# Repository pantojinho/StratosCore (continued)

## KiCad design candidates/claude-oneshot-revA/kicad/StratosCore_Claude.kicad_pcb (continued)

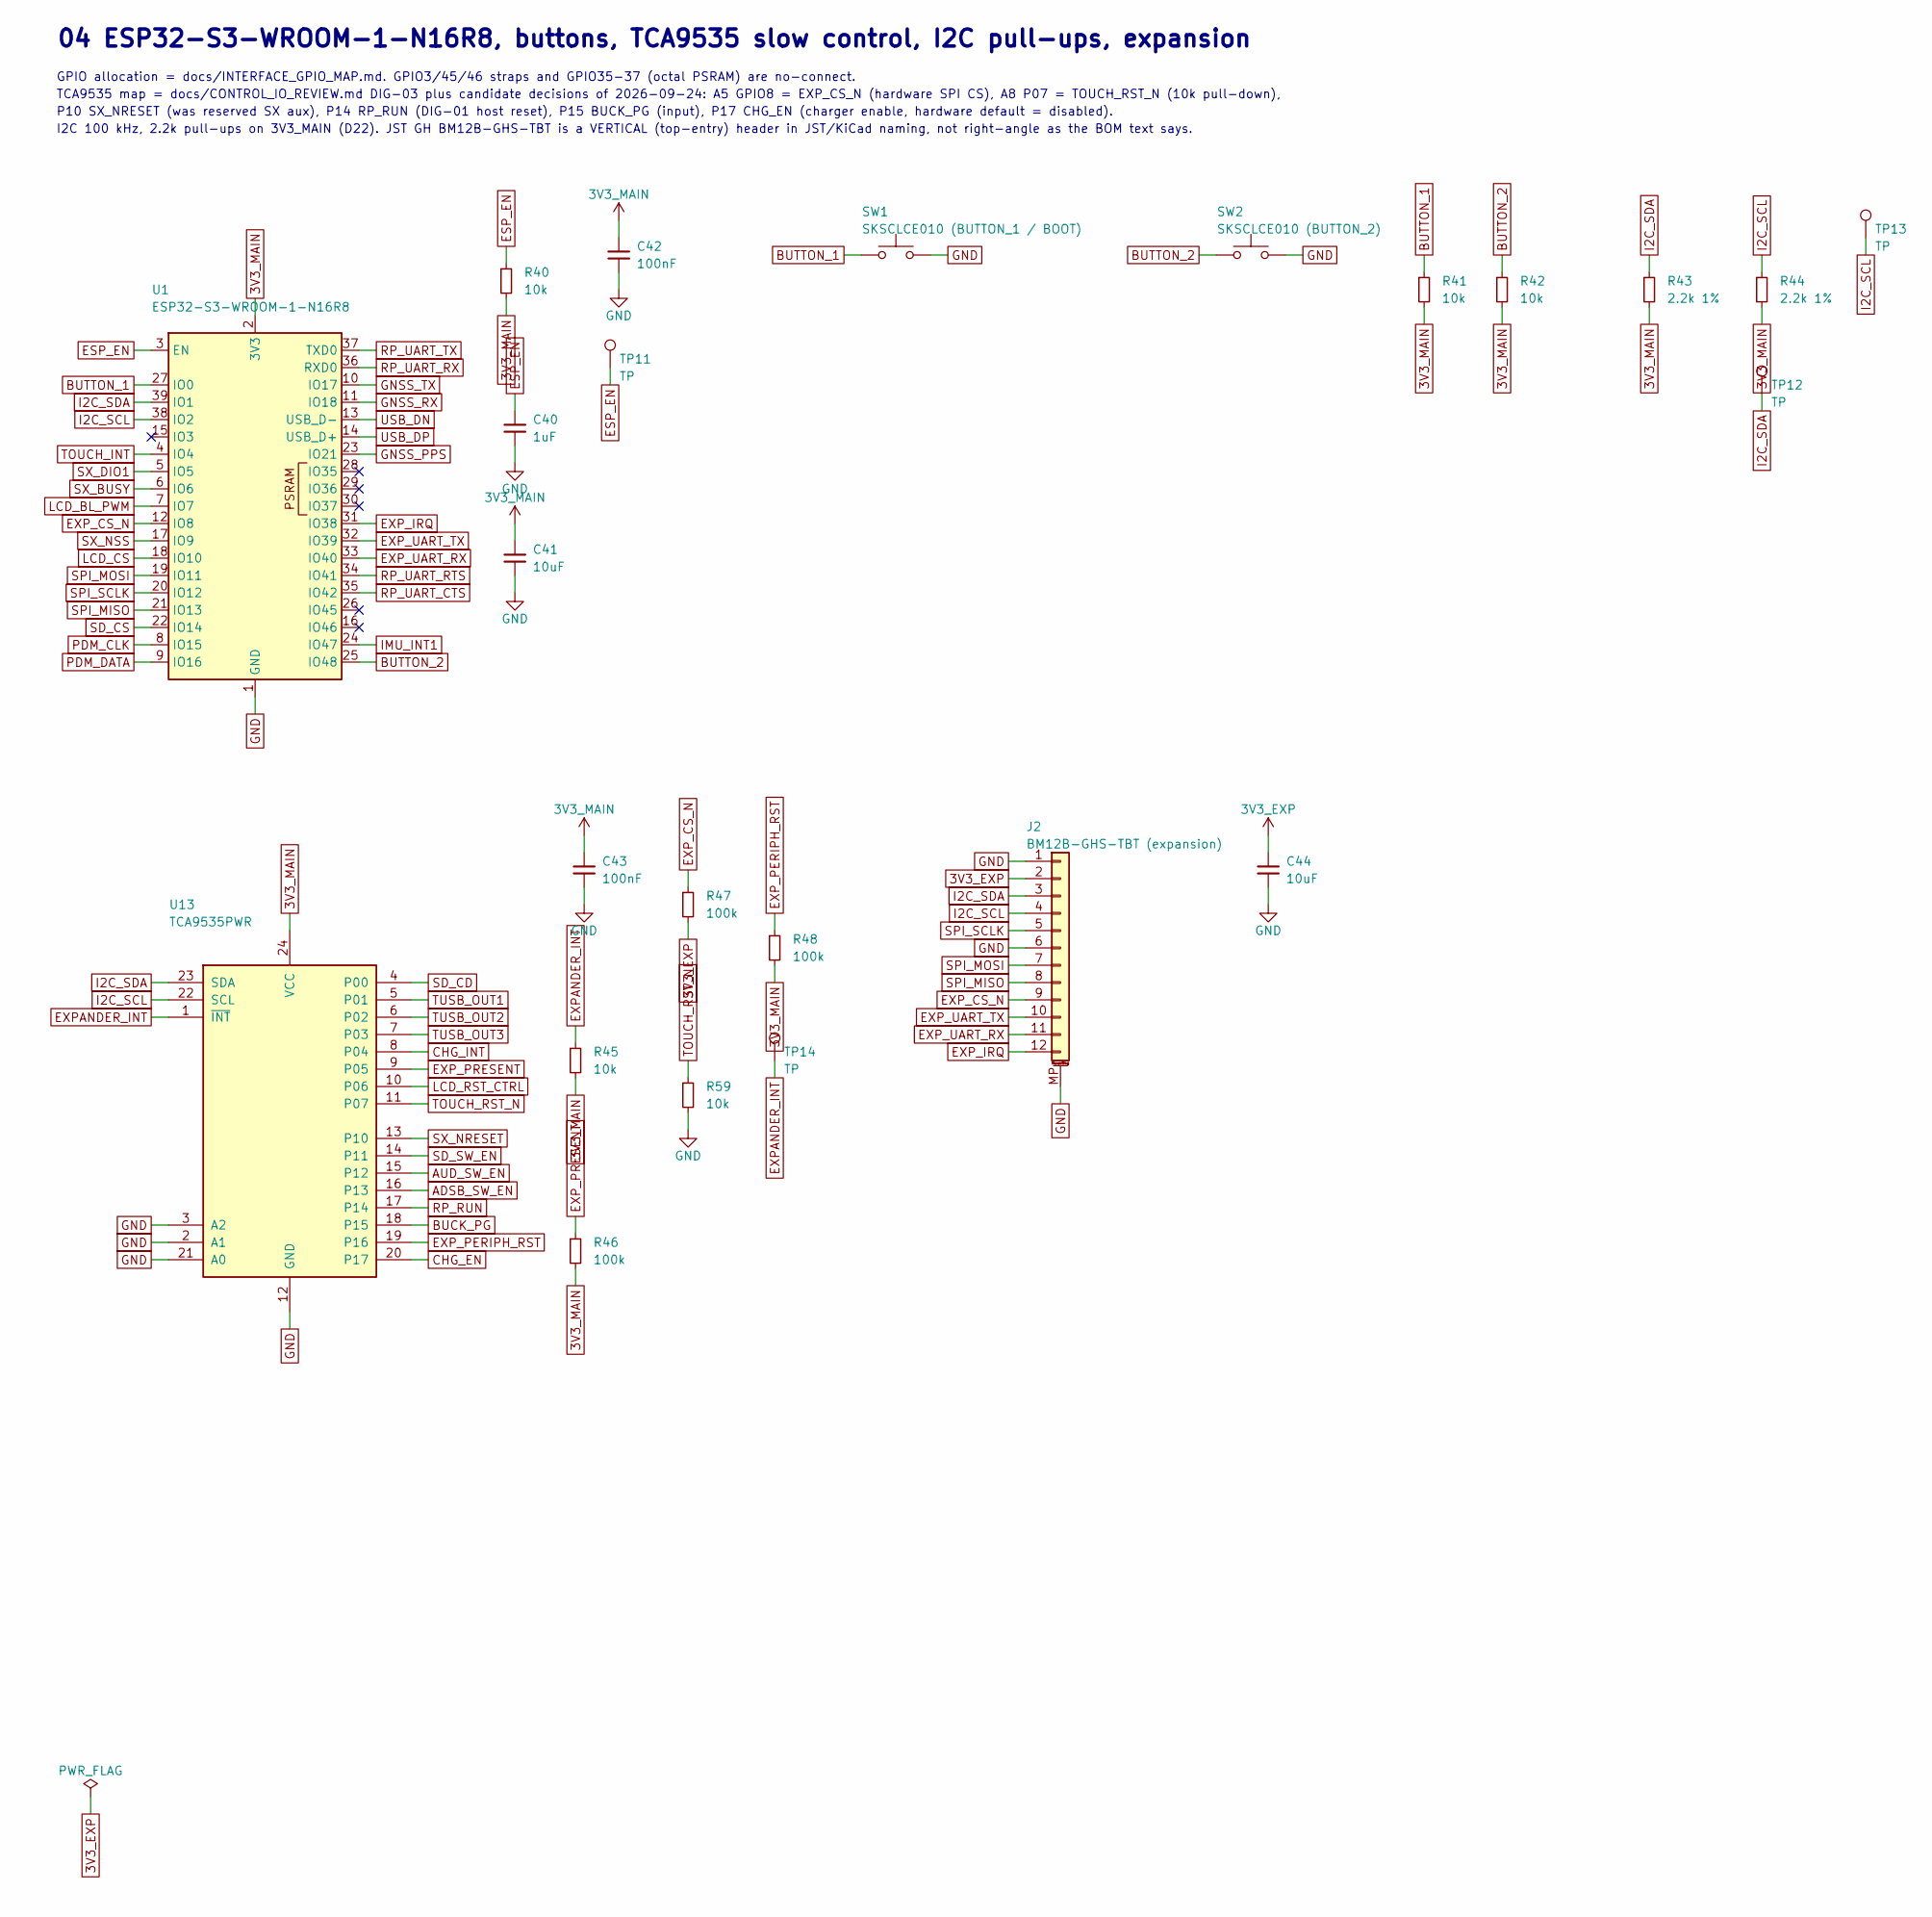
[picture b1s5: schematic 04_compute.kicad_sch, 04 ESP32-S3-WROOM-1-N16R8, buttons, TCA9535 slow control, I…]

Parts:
C40: 1uF; C_0402_1005Metric
C41, C44: 10uF; C_0603_1608Metric
C42, C43: 100nF; C_0402_1005Metric
J2: BM12B-GHS-TBT (expansion); JST_GH_BM12B-GHS-TBT_1x12-1MP_P1.25mm_Vertical; MPN BM12B-GHS-TBT
R40, R41, R42, R45, R59: 10k; R_0402_1005Metric
R43, R44: 2.2k 1%; R_0402_1005Metric
R46, R47, R48: 100k; R_0402_1005Metric
SW1: SKSCLCE010 (BUTTON_1 / BOOT); SW_Alps_SKSCLCE010_SidePush; MPN SKSCLCE010
SW2: SKSCLCE010 (BUTTON_2); SW_Alps_SKSCLCE010_SidePush; MPN SKSCLCE010
TP11, TP12, TP13, TP14: TP; TestPoint_Pad_D1.0mm
U1: ESP32-S3-WROOM-1-N16R8; ESP32-S3-WROOM-1; MPN ESP32-S3-WROOM-1-N16R8
U13: TCA9535PWR; TI_PW0024A_TSSOP-24_4.4x7.8mm_TCA9535; MPN TCA9535PWR

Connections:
3V3_EXP: C44.1, J2.2, R47.2; also elsewhere on the board
3V3_MAIN: C41.1, C42.1, C43.1, R40.2, R41.2, R42.2, R43.2, R44.2, R45.2, R46.2, R48.2, U1.2 (3V3), U13.24 (VCC); also elsewhere on the board
ADSB_SW_EN: U13.16 (P13); also elsewhere on the board
AUD_SW_EN: U13.15 (P12); also elsewhere on the board
BUCK_PG: U13.18 (P15); also elsewhere on the board
BUTTON_1: R41.1, SW1.1, U1.27 (IO0)
BUTTON_2: R42.1, SW2.1, U1.25 (IO48)
CHG_EN: U13.20 (P17); also elsewhere on the board
CHG_INT: U13.8 (P04); also elsewhere on the board
ESP_EN: C40.1, R40.1, TP11.1, U1.3 (EN)
EXPANDER_INT: R45.1, TP14.1, U13.1 (~INT)
EXP_CS_N: J2.9, R47.1, U1.12 (IO8)
EXP_IRQ: J2.12, U1.31 (IO38)
EXP_PERIPH_RST: R48.1, U13.19 (P16)
EXP_PRESENT: R46.1, U13.9 (P05)
EXP_UART_RX: J2.11, U1.33 (IO40)
EXP_UART_TX: J2.10, U1.32 (IO39)
GND: C40.2, C41.2, C42.2, C43.2, C44.2, J2.1, J2.6, J2.MP (MountPin), R59.2, SW1.2, SW2.2, U1.1 (GND), U1.40 (GND), U1.41 (GND), U13.2 (A1), U13.3 (A2), U13.12 (GND), U13.21 (A0); also elsewhere on the board
GNSS_PPS: U1.23 (IO21); also elsewhere on the board
GNSS_RX: U1.11 (IO18); also elsewhere on the board
GNSS_TX: U1.10 (IO17); also elsewhere on the board
I2C_SCL: J2.4, R44.1, TP13.1, U1.38 (IO2), U13.22 (SCL); also elsewhere on the board
I2C_SDA: J2.3, R43.1, TP12.1, U1.39 (IO1), U13.23 (SDA); also elsewhere on the board
IMU_INT1: U1.24 (IO47); also elsewhere on the board
LCD_BL_PWM: U1.7 (IO7); also elsewhere on the board
LCD_CS: U1.18 (IO10); also elsewhere on the board
LCD_RST_CTRL: U13.10 (P06); also elsewhere on the board
PDM_CLK: U1.8 (IO15); also elsewhere on the board
PDM_DATA: U1.9 (IO16); also elsewhere on the board
RP_RUN: U13.17 (P14); also elsewhere on the board
RP_UART_CTS: U1.35 (IO42); also elsewhere on the board
RP_UART_RTS: U1.34 (IO41); also elsewhere on the board
RP_UART_RX: U1.36 (RXD0); also elsewhere on the board
RP_UART_TX: U1.37 (TXD0); also elsewhere on the board
SD_CD: U13.4 (P00); also elsewhere on the board
SD_CS: U1.22 (IO14); also elsewhere on the board
SD_SW_EN: U13.14 (P11); also elsewhere on the board
SPI_MISO: J2.8, U1.21 (IO13); also elsewhere on the board
SPI_MOSI: J2.7, U1.19 (IO11); also elsewhere on the board
SPI_SCLK: J2.5, U1.20 (IO12); also elsewhere on the board
SX_BUSY: U1.6 (IO6); also elsewhere on the board
SX_DIO1: U1.5 (IO5); also elsewhere on the board
SX_NRESET: U13.13 (P10); also elsewhere on the board
SX_NSS: U1.17 (IO9); also elsewhere on the board
TOUCH_INT: U1.4 (IO4); also elsewhere on the board
TOUCH_RST_N: R59.1, U13.11 (P07); also elsewhere on the board
TUSB_OUT1: U13.5 (P01); also elsewhere on the board
TUSB_OUT2: U13.6 (P02); also elsewhere on the board
TUSB_OUT3: U13.7 (P03); also elsewhere on the board
USB_DN: U1.13 (USB_D-); also elsewhere on the board
USB_DP: U1.14 (USB_D+); also elsewhere on the board

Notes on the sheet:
04 ESP32-S3-WROOM-1-N16R8, buttons, TCA9535 slow control, I2C pull-ups, expansion
GPIO allocation = docs/INTERFACE_GPIO_MAP.md. GPIO3/45/46 straps and GPIO35-37 (octal PSRAM) are no-connect.
TCA9535 map = docs/CONTROL_IO_REVIEW.md DIG-03 plus candidate decisions of 2026-09-24: A5 GPIO8 = EXP_CS_N (hardware SPI CS), A8 P07 = TOUCH_RST_N (10k pull-down),
P10 SX_NRESET (was reserved SX aux), P14 RP_RUN (DIG-01 host reset), P15 BUCK_PG (input), P17 CHG_EN (charger enable, hardware default = disabled).
I2C 100 kHz, 2.2k pull-ups on 3V3_MAIN (D22). JST GH BM12B-GHS-TBT is a VERTICAL (top-entry) header in JST/KiCad naming, not right-angle as the BOM text says.

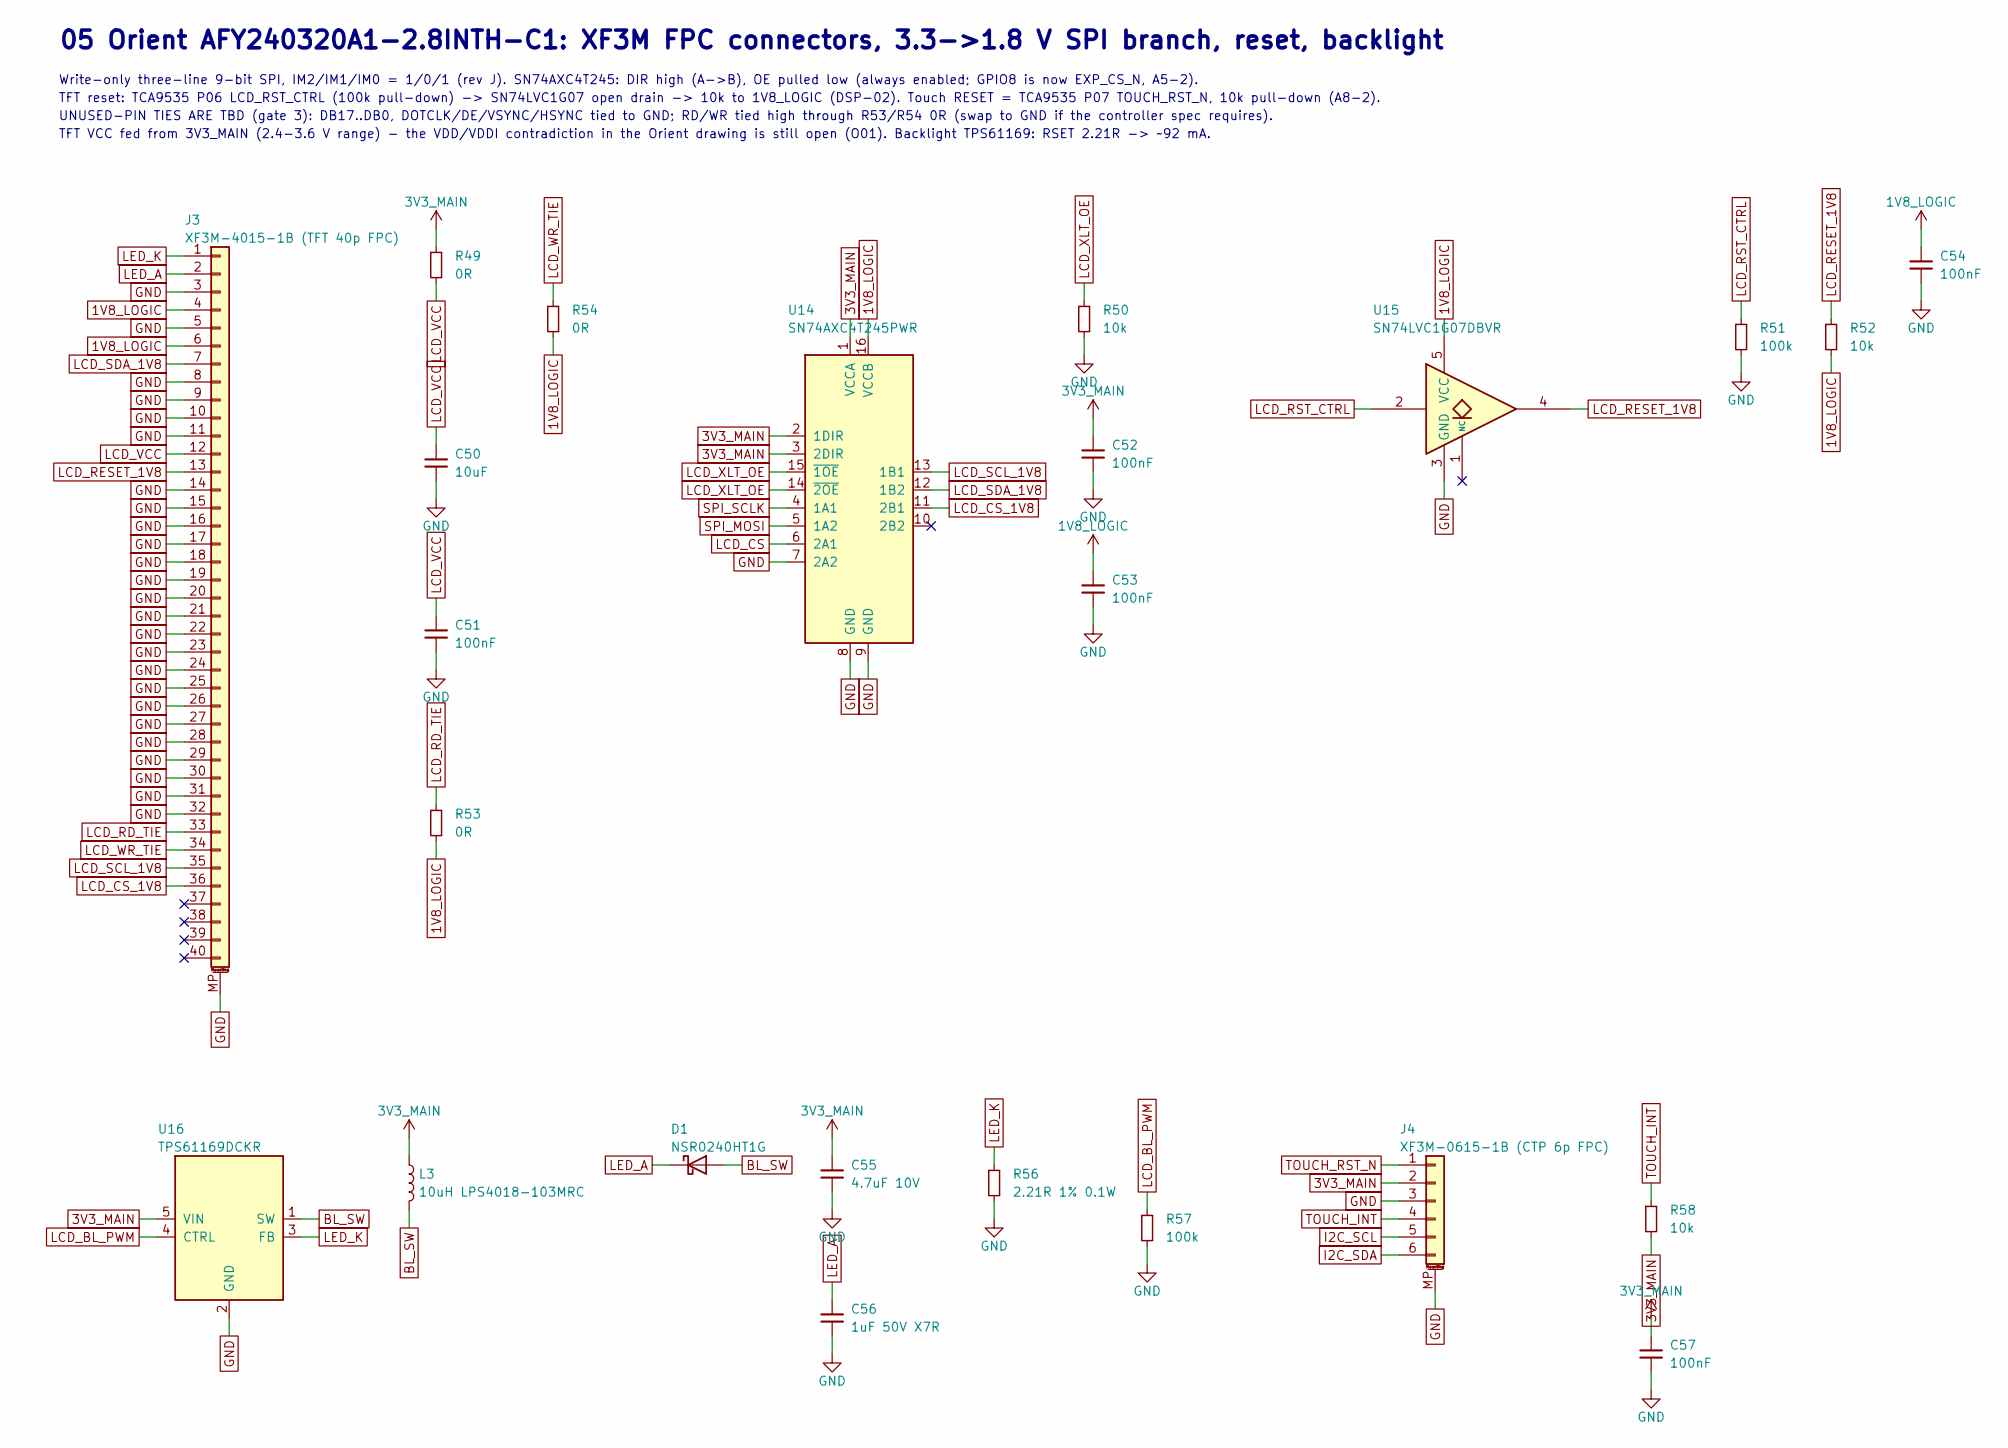
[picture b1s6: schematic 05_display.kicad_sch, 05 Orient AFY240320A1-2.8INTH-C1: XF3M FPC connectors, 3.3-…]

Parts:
C50: 10uF; C_0603_1608Metric
C51, C52, C53, C54, C57: 100nF; C_0402_1005Metric
C55: 4.7uF 10V; C_0603_1608Metric
C56: 1uF 50V X7R; C_0805_2012Metric
D1: NSR0240HT1G; D_SOD-323; MPN NSR0240HT1G
J3: XF3M-4015-1B (TFT 40p FPC); Omron_XF3M-4015-1B_1x40-1MP_P0.5mm_Horizontal; MPN XF3M-4015-1B
J4: XF3M-0615-1B (CTP 6p FPC); Omron_XF3M-0615-1B_1x06-1MP_P0.5mm_Horizontal; MPN XF3M-0615-1B
L3: 10uH LPS4018-103MRC; L_Coilcraft_LPS4018; MPN LPS4018-103MRC
R49: 0R; R_0603_1608Metric
R50, R52, R58: 10k; R_0402_1005Metric
R51, R57: 100k; R_0402_1005Metric
R53, R54: 0R; R_0402_1005Metric
R56: 2.21R 1% 0.1W; R_0603_1608Metric
U14: SN74AXC4T245PWR; TSSOP-16_4.4x5mm_P0.65mm; MPN SN74AXC4T245PWR
U15: SN74LVC1G07DBVR; SOT-23-5; MPN SN74LVC1G07DBVR
U16: TPS61169DCKR; TI_DCK0005A_SC-70-5_TPS61169; MPN TPS61169DCKR

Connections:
1V8_LOGIC: C53.1, C54.1, J3.4, J3.6, R52.2, R53.2, R54.2, U14.16 (VCCB), U15.5 (VCC); also elsewhere on the board
3V3_MAIN: C52.1, C55.1, C57.1, J4.2, L3.1, R49.1, R58.2, U14.1 (VCCA), U14.2 (1DIR), U14.3 (2DIR), U16.5 (VIN); also elsewhere on the board
BL_SW: D1.2 (A), L3.2, U16.1 (SW)
GND: C50.2, C51.2, C52.2, C53.2, C54.2, C55.2, C56.2, C57.2, J3.3, J3.5, J3.8, J3.9, J3.10, J3.11, J3.14, J3.15, J3.16, J3.17, J3.18, J3.19, J3.20, J3.21, J3.22, J3.23, J3.24, J3.25, J3.26, J3.27, J3.28, J3.29, J3.30, J3.31, J3.32, J3.MP (MountPin), J4.3, J4.MP (MountPin), R50.2, R51.2, R56.2, R57.2, U14.7 (2A2), U14.8 (GND), U14.9 (GND), U15.3 (GND), U16.2 (GND); also elsewhere on the board
I2C_SCL: J4.5; also elsewhere on the board
I2C_SDA: J4.6; also elsewhere on the board
LCD_BL_PWM: R57.1, U16.4 (CTRL); also elsewhere on the board
LCD_CS: U14.6 (2A1); also elsewhere on the board
LCD_CS_1V8: J3.36, U14.11 (2B1)
LCD_RD_TIE: J3.33, R53.1
LCD_RESET_1V8: J3.13, R52.1, U15.4
LCD_RST_CTRL: R51.1, U15.2; also elsewhere on the board
LCD_SCL_1V8: J3.35, U14.13 (1B1)
LCD_SDA_1V8: J3.7, U14.12 (1B2)
LCD_VCC: C50.1, C51.1, J3.12, R49.2
LCD_WR_TIE: J3.34, R54.1
LCD_XLT_OE: R50.1, U14.14 (~2OE), U14.15 (~1OE)
LED_A: C56.1, D1.1 (K), J3.2
LED_K: J3.1, R56.1, U16.3 (FB)
SPI_MOSI: U14.5 (1A2); also elsewhere on the board
SPI_SCLK: U14.4 (1A1); also elsewhere on the board
TOUCH_INT: J4.4, R58.1; also elsewhere on the board
TOUCH_RST_N: J4.1; also elsewhere on the board

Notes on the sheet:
05 Orient AFY240320A1-2.8INTH-C1: XF3M FPC connectors, 3.3->1.8 V SPI branch, reset, backlight
Write-only three-line 9-bit SPI, IM2/IM1/IM0 = 1/0/1 (rev J). SN74AXC4T245: DIR high (A->B), OE pulled low (always enabled; GPIO8 is now EXP_CS_N, A5-2).
TFT reset: TCA9535 P06 LCD_RST_CTRL (100k pull-down) -> SN74LVC1G07 open drain -> 10k to 1V8_LOGIC (DSP-02). Touch RESET = TCA9535 P07 TOUCH_RST_N, 10k pull-down (A8-2).
UNUSED-PIN TIES ARE TBD (gate 3): DB17..DB0, DOTCLK/DE/VSYNC/HSYNC tied to GND; RD/WR tied high through R53/R54 0R (swap to GND if the controller spec requires).
TFT VCC fed from 3V3_MAIN (2.4-3.6 V range) - the VDD/VDDI contradiction in the Orient drawing is still open (O01). Backlight TPS61169: RSET 2.21R -> ~92 mA.

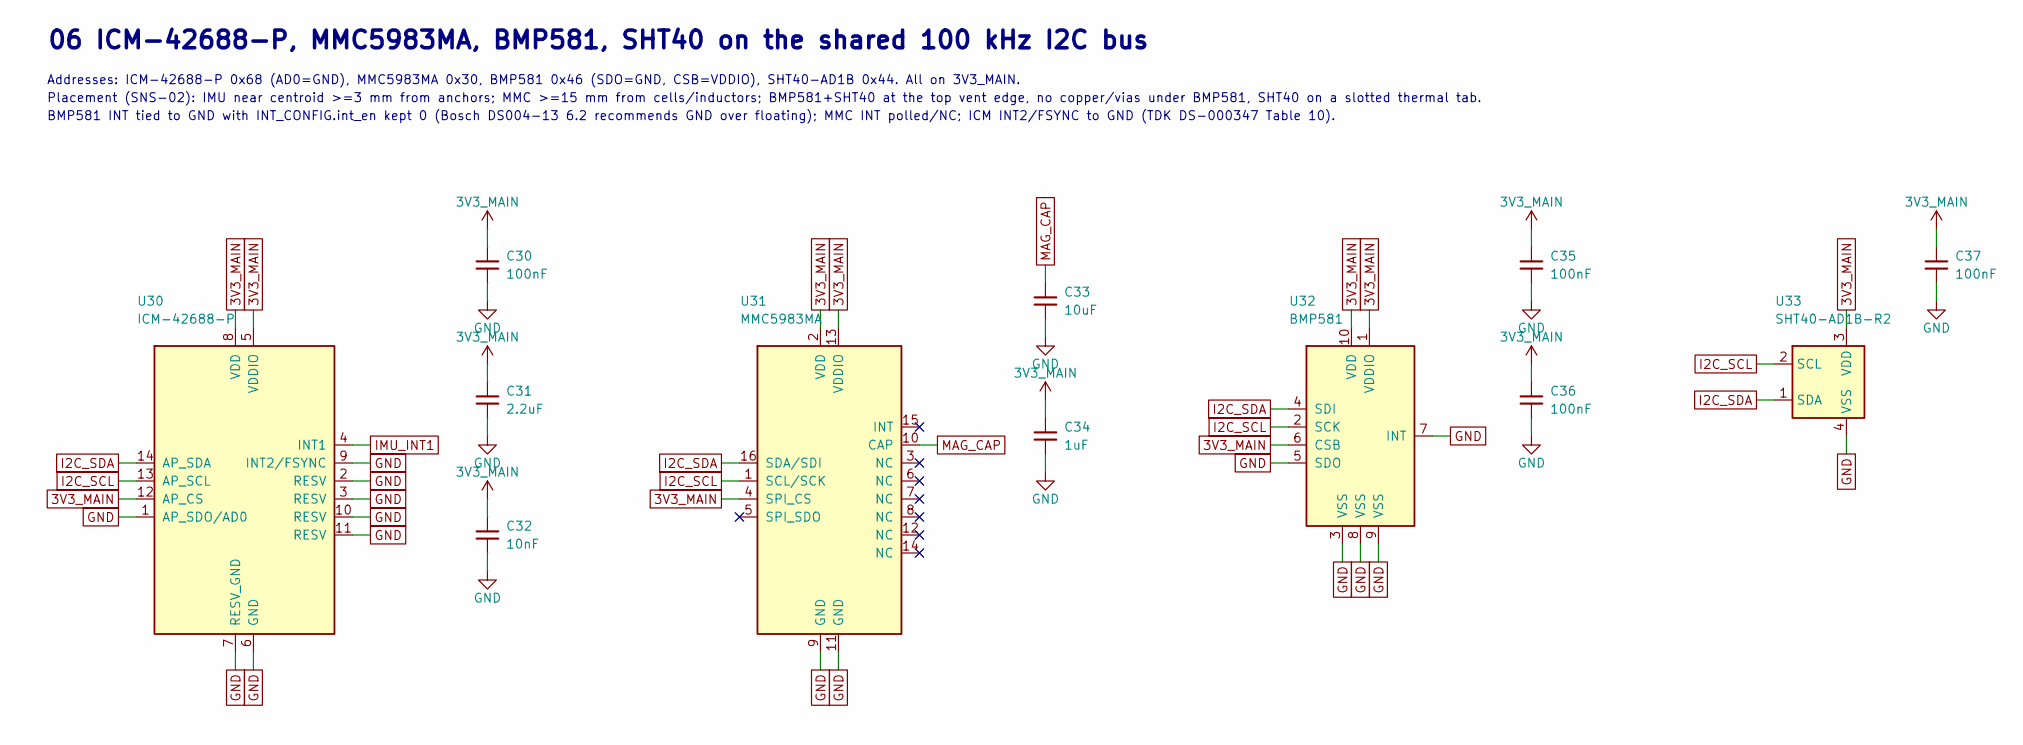
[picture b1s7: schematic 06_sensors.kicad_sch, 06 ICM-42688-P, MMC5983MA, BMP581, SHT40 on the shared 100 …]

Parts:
C30, C35, C36, C37: 100nF; C_0402_1005Metric
C31: 2.2uF; C_0402_1005Metric
C32: 10nF; C_0402_1005Metric
C33: 10uF; C_0603_1608Metric
C34: 1uF; C_0402_1005Metric
U30: ICM-42688-P; TDK_ICM-42688-P_LGA-14_3x2.5mm_P0.5mm; MPN ICM-42688-P
U31: MMC5983MA; MEMSIC_MMC5983MA_LGA-16_3x3mm_P0.5mm_CORRECTED; MPN MMC5983MA
U32: BMP581; Bosch_BMP581_LGA-10_2x2mm_CORRECTED; MPN BMP581
U33: SHT40-AD1B-R2; Sensirion_DFN-4_1.5x1.5mm_P0.8mm_SHT4x_NoCentralPad; MPN SHT40-AD1B-R2

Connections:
3V3_MAIN: C30.1, C31.1, C32.1, C34.1, C35.1, C36.1, C37.1, U30.5 (VDDIO), U30.8 (VDD), U30.12 (AP_CS), U31.2 (VDD), U31.4 (SPI_CS), U31.13 (VDDIO), U32.1 (VDDIO), U32.6 (CSB), U32.10 (VDD), U33.3 (VDD); also elsewhere on the board
GND: C30.2, C31.2, C32.2, C33.2, C34.2, C35.2, C36.2, C37.2, U30.1 (AP_SDO/AD0), U30.2 (RESV), U30.3 (RESV), U30.6 (GND), U30.7 (RESV_GND), U30.9 (INT2/FSYNC), U30.10 (RESV), U30.11 (RESV), U31.9 (GND), U31.11 (GND), U32.3 (VSS), U32.5 (SDO), U32.7 (INT), U32.8 (VSS), U32.9 (VSS), U33.4 (VSS); also elsewhere on the board
I2C_SCL: U30.13 (AP_SCL), U31.1 (SCL/SCK), U32.2 (SCK), U33.2 (SCL); also elsewhere on the board
I2C_SDA: U30.14 (AP_SDA), U31.16 (SDA/SDI), U32.4 (SDI), U33.1 (SDA); also elsewhere on the board
IMU_INT1: U30.4 (INT1); also elsewhere on the board
MAG_CAP: C33.1, U31.10 (CAP)

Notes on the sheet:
06 ICM-42688-P, MMC5983MA, BMP581, SHT40 on the shared 100 kHz I2C bus
Addresses: ICM-42688-P 0x68 (AD0=GND), MMC5983MA 0x30, BMP581 0x46 (SDO=GND, CSB=VDDIO), SHT40-AD1B 0x44. All on 3V3_MAIN.
Placement (SNS-02): IMU near centroid >=3 mm from anchors; MMC >=15 mm from cells/inductors; BMP581+SHT40 at the top vent edge, no copper/vias under BMP581, SHT40 on a slotted thermal tab.
BMP581 INT tied to GND with INT_CONFIG.int_en kept 0 (Bosch DS004-13 6.2 recommends GND over floating); MMC INT polled/NC; ICM INT2/FSYNC to GND (TDK DS-000347 Table 10).

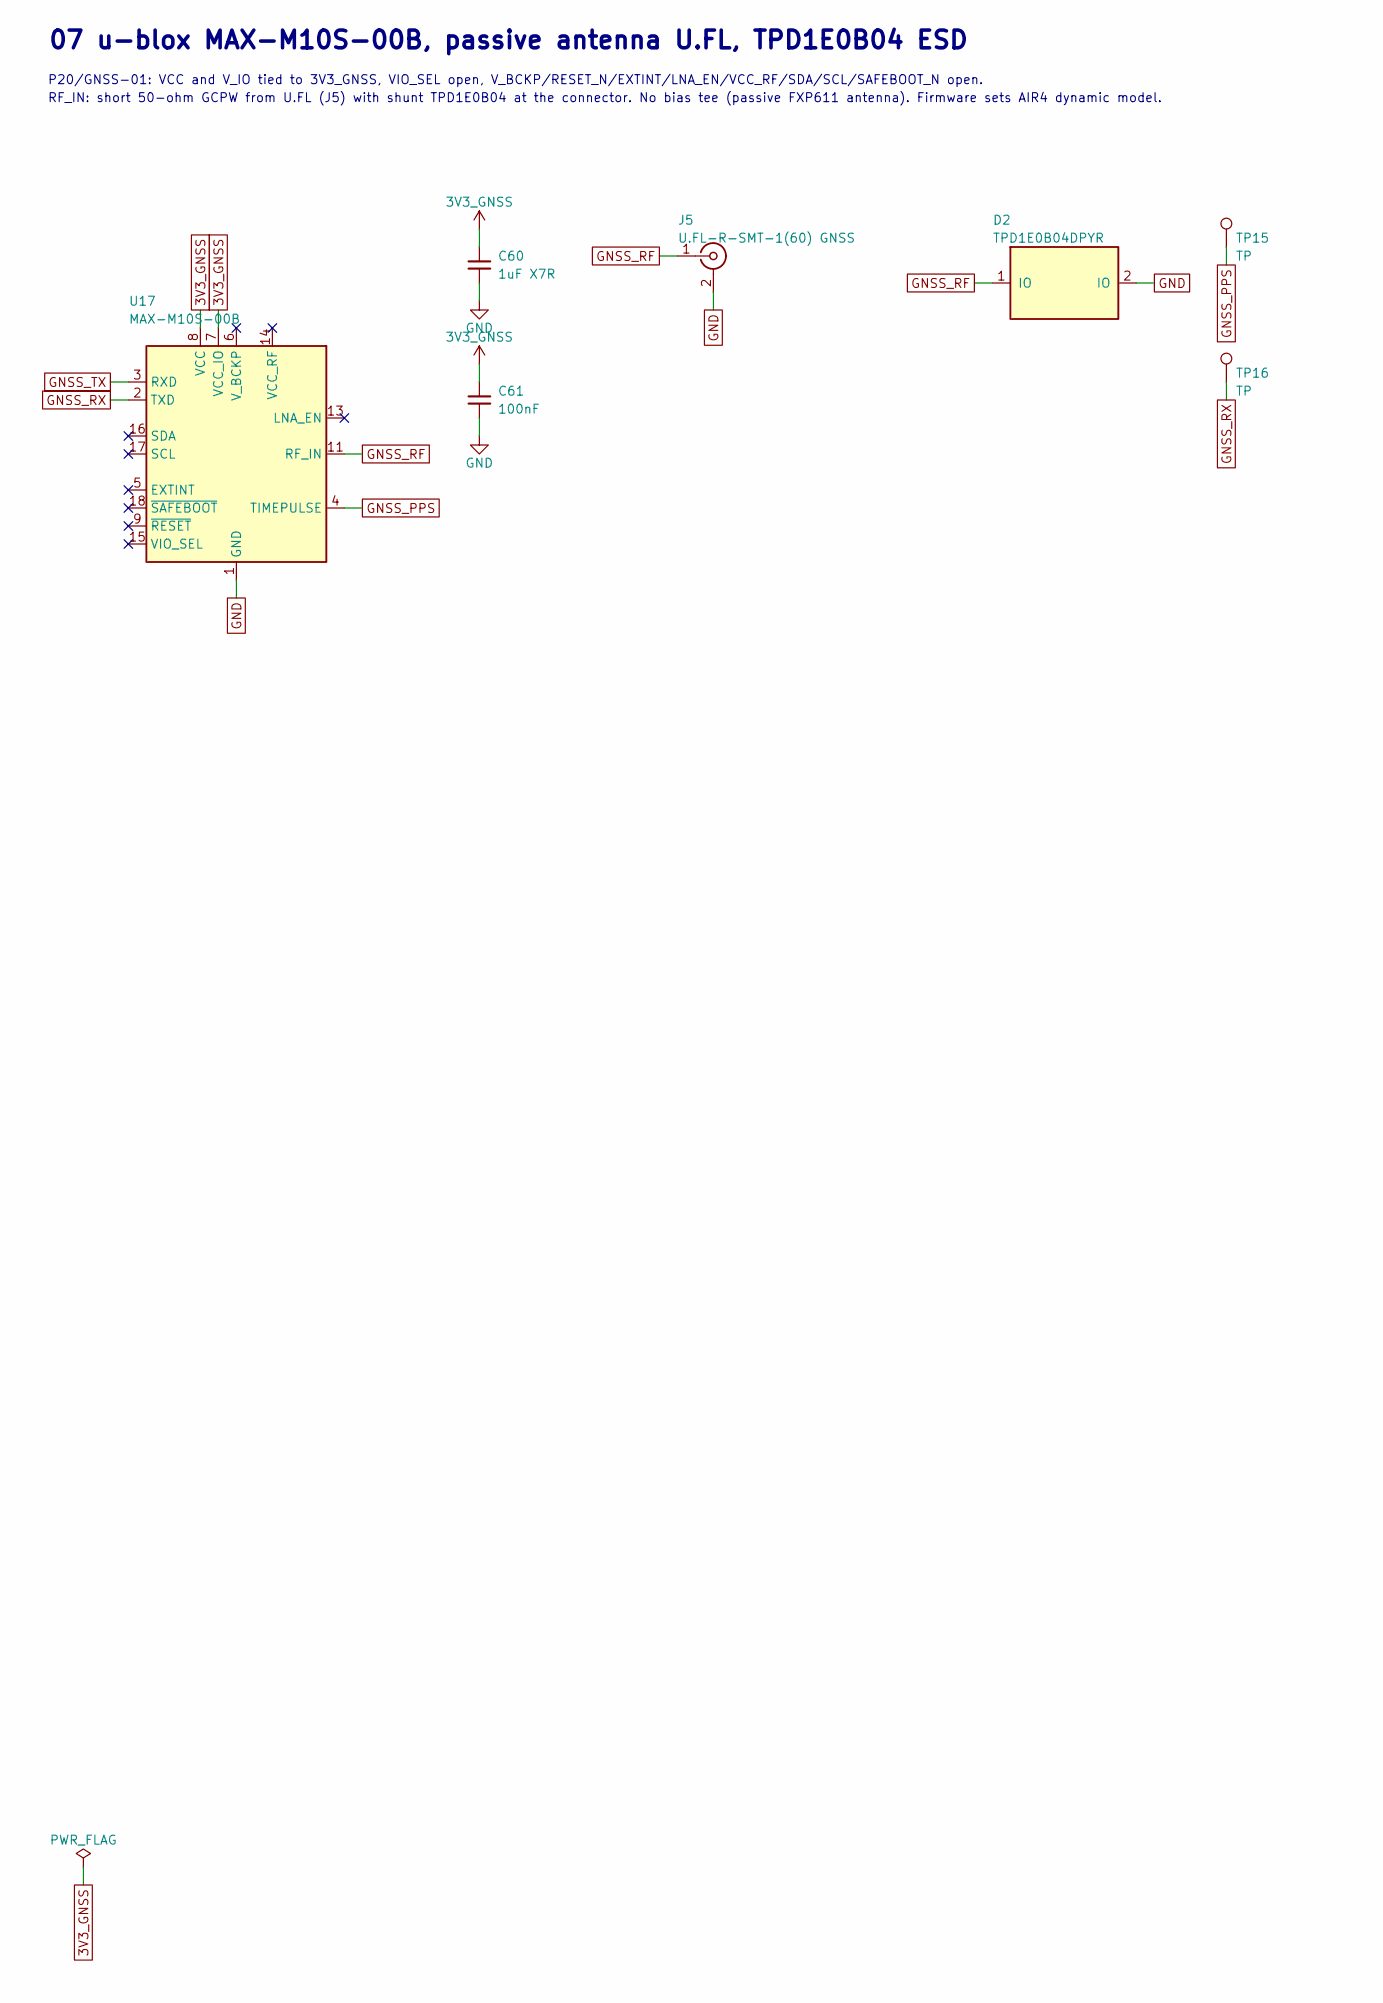
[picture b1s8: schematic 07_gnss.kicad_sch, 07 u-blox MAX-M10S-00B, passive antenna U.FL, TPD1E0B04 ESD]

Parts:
C60: 1uF X7R; C_0402_1005Metric
C61: 100nF; C_0402_1005Metric
D2: TPD1E0B04DPYR; TI_TPD1E0B04DPYR_X1SON-2_DPY0002A; MPN TPD1E0B04DPYR
J5: U.FL-R-SMT-1(60) GNSS; Hirose_U.FL-R-SMT-1_60_Vertical; MPN U.FL-R-SMT-1(60)
TP15, TP16: TP; TestPoint_Pad_D1.0mm
U17: MAX-M10S-00B; u-blox_MAX-M10S-00B_LCC-18_10.1x9.7mm; MPN MAX-M10S-00B

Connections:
3V3_GNSS: C60.1, C61.1, U17.7 (VCC_IO), U17.8 (VCC); also elsewhere on the board
GND: C60.2, C61.2, D2.2, J5.2 (Ext), U17.1 (GND), U17.10 (GND), U17.12 (GND); also elsewhere on the board
GNSS_PPS: TP15.1, U17.4 (TIMEPULSE); also elsewhere on the board
GNSS_RF: D2.1, J5.1 (In), U17.11 (RF_IN)
GNSS_RX: TP16.1, U17.2 (TXD); also elsewhere on the board
GNSS_TX: U17.3 (RXD); also elsewhere on the board

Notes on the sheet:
07 u-blox MAX-M10S-00B, passive antenna U.FL, TPD1E0B04 ESD
P20/GNSS-01: VCC and V_IO tied to 3V3_GNSS, VIO_SEL open, V_BCKP/RESET_N/EXTINT/LNA_EN/VCC_RF/SDA/SCL/SAFEBOOT_N open.
RF_IN: short 50-ohm GCPW from U.FL (J5) with shunt TPD1E0B04 at the connector. No bias tee (passive FXP611 antenna). Firmware sets AIR4 dynamic model.

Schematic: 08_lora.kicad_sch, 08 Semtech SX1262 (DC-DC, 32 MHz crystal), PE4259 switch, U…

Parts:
C70: 10uF; C_0603_1608Metric
C71: 1uF; C_0402_1005Metric
C72: 100nF; C_0402_1005Metric
C73: 470nF; C_0402_1005Metric
C74: 47nF; C_0402_1005Metric
C75: DNP (E449 C3); C_0402_1005Metric; not fitted
C76: 5.6pF C0G; C_0402_1005Metric
C77, C80: 1.8pF C0G; C_0402_1005Metric
C78, C83: 39pF C0G; C_0402_1005Metric
C79: 2.4pF C0G; C_0402_1005Metric
C81, C82: 1nF; C_0402_1005Metric
C84: 47pF C0G; C_0402_1005Metric
C85: 3.0pF C0G; C_0402_1005Metric
C86: DNP (E449 C13); C_0402_1005Metric; not fitted
C87, C89: 3.3pF C0G; C_0402_1005Metric
J6: U.FL-R-SMT-1(60) LoRa; Hirose_U.FL-R-SMT-1_60_Vertical; MPN U.FL-R-SMT-1(60)
L70: 15uH MLZ2012M150W; L_0805_2012Metric; MPN MLZ2012M150WT000
L71: 47nH LQW15AN47NJ00; L_0402_1005Metric; MPN LQW15AN47NJ00D
L72: 2.5nH LQW15AN2N5C00; L_0402_1005Metric; MPN LQW15AN2N5C00D
L73: 4.7nH LQW15AN4N7C00; L_0402_1005Metric; MPN LQW15AN4N7C00D
L74: 15nH LQW15AN15NH00; L_0402_1005Metric; MPN LQW15AN15NH00D
L75: 9.1nH LQW15AN9N1H00; L_0402_1005Metric; MPN LQW15AN9N1H00D
R70: 100k; R_0402_1005Metric
R71: 100R; R_0402_1005Metric
R72: 1k; R_0402_1005Metric
R73: 0R; R_0402_1005Metric
R74: 15k; R_0402_1005Metric
U40: SX1262IMLTRT; QFN-24-1EP_4x4mm_P0.5mm_EP2.6x2.6mm; MPN SX1262IMLTRT
U41: PE4259; SOT-363_SC-70-6; MPN PE4259-63
Y2: 32MHz NX2016SA CL10pF; Crystal_SMD_2016-4Pin_2.0x1.6mm; MPN NX2016SA-32MHz-EXS00A-CS06465

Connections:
3V3_MAIN: C70.1, C71.1, C72.1, R70.2, R72.1, U40.1 (VDD_IN), U40.10 (VBAT), U40.11 (VBAT_IO); also elsewhere on the board
GND: C70.2, C71.2, C72.2, C73.2, C74.2, C75.2, C76.2, C77.2, C80.2, C81.2, C82.2, C84.2, C86.2, C87.2, C89.2, J6.2 (Ext), R74.2, U40.2 (GND), U40.5 (GND), U40.8 (GND), U40.20 (GND), U40.25 (GND), U41.2 (GND), Y2.2 (G), Y2.4 (G); also elsewhere on the board
LORA_ANT: C89.1, J6.1 (In), L75.2
LORA_ANTF: C83.2, C87.1, L75.1
LORA_PA: C75.1, C85.1, L71.2, L72.1, R73.2
LORA_RFC: C83.1, U41.5 (RFC)
LORA_RFI_N: C79.2, L74.1, U40.22 (RFI_N)
LORA_RFI_P: C80.1, L74.2, U40.21 (RFI_P)
LORA_RFO: R73.1, U40.23 (RFO)
LORA_RX_SW: C79.1, C86.1, U41.3 (RF2)
LORA_SW_CTRL: C81.1, R71.2, U41.4 (CTRL)
LORA_SW_VDD: C82.1, R72.2, R74.1, U41.6 (VDD/CTRL_N)
LORA_TXF1: C76.1, C78.1, C85.2, L72.2
LORA_TXF2: C78.2, L73.1
LORA_TX_SW: C77.1, L73.2, U41.1 (RF1)
SPI_MISO: U40.16 (MISO); also elsewhere on the board
SPI_MOSI: U40.17 (MOSI); also elsewhere on the board
SPI_SCLK: U40.18 (SCK); also elsewhere on the board
SX_BUSY: U40.14 (BUSY); also elsewhere on the board
SX_DCC_SW: L70.1, U40.9 (DCC_SW)
SX_DIO1: U40.13 (DIO1); also elsewhere on the board
SX_DIO2: R71.1, U40.12 (DIO2)
SX_NRESET: R70.1, U40.15 (~RESET); also elsewhere on the board
SX_NSS: U40.19 (NSS); also elsewhere on the board
SX_VREG: C73.1, L70.2, U40.7 (VREG)
SX_VR_PA: C74.1, C84.1, L71.1, U40.24 (VR_PA)
SX_XTA: U40.3 (XTA), Y2.1
SX_XTB: U40.4 (XTB), Y2.3

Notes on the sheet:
08 Semtech SX1262 (DC-DC, 32 MHz crystal), PE4259 switch, U.FL
A2: RF network redrawn to the Semtech E449V01A / E428V03A reference topology (same RF values in both 902-928 MHz boards) with the reference BOM values as STARTING values.
*** The values were tuned by Semtech on a 1.0 mm stack (0.15 mm L1-L2). On JLC04161H-3313 they must be re-tuned on a VNA and pass conducted TX power/harmonic/RX tests (AGENTS rule 5). Not validated. ***
Crystal (E428-type) kept by the lowest-cost criterion: NDK NX2016SA 32 MHz EXS00A-CS06465 (CL 10 pF, +/-10 ppm). TCXO (E449) is the owner option if long-airtime plans are used; DIO3 left open.
PE4259 single-pin mode: pin 6 = VDD through R72/R74 divider (about 3.09 V; pSemi operating range is 1.8-3.3 V and 3V3_MAIN can exceed 3.3 V with tolerance). DIO2 = 1 in TX selects RF1. No TX before a regional configuration (AGENTS rule 14).

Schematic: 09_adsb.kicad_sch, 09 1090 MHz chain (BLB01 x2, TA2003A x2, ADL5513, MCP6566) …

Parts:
C88, C108, C109: 1uF; C_0402_1005Metric
C90, C98, C800, C802, C840, C842: 100pF; C_0402_1005Metric
C91: 10uF; C_0603_1608Metric
C95, C96: 47nF; C_0402_1005Metric
C97, C100, C101, C102, C103, C104, C105, C106, C107, C110, C111, C112, C113, C116: 100nF; C_0402_1005Metric
C99: 1nF; C_0402_1005Metric; not fitted
C114, C115: 15pF C0G; C_0402_1005Metric
C801, C803, C841, C843: 12pF; C_0402_1005Metric
D3: TPD1E0B04DPYR (option); TI_TPD1E0B04DPYR_X1SON-2_DPY0002A; not fitted
FL1, FL2: TA2003A 1090MHz SAW; TAI-SAW_TA2003A_SMD-6_3.0x3.0mm; MPN TA2003A
J7: U.FL-R-SMT-1(60) ADS-B; Hirose_U.FL-R-SMT-1_60_Vertical; MPN U.FL-R-SMT-1(60)
L800, L840: 27nH; L_0603_1608Metric
L801, L841: 82nH; L_0603_1608Metric
R86: TBD (OWN-09); R_0402_1005Metric; not fitted
R87, R90: 100k; R_0402_1005Metric
R88, R91: 10k; R_0402_1005Metric
R89, R92, R93: 1k; R_0402_1005Metric
R94, R99: 27R 1%; R_0402_1005Metric
R95: 52.3R 1%; R_0402_1005Metric
R96, R801, R841: 0R; R_0402_1005Metric
R97: TBD (TADJ @1090 MHz); R_0402_1005Metric
R98: 2.2k 1%; R_0402_1005Metric
R800, R840: 6.8k; R_0402_1005Metric
TP20, TP21, TP22, TP23, TP24, TP25, TP26, TP29, TP30: TP; TestPoint_Pad_D1.0mm
U11: TPS22918DBVR; TI_DBV0006A_SOT-23-6_TPS22918; MPN TPS22918DBVR
U20: RP2040; QFN-56-1EP_7x7mm_P0.4mm_EP3.2x3.2mm; MPN RP2040
U21: W25Q128JVSIQ; Winbond_W25Q128JVSIQ_SOIC-8_5.3x5.3mm_P1.27mm; MPN W25Q128JVSIQ
U50, U52: BLB01; BeRex_BLB01_DFN-8-1EP_2x2mm_P0.5mm; MPN BLB01
U54: ADL5513ACPZ-R7; LFCSP-16-1EP_3x3mm_P0.5mm_EP1.7x1.7mm; MPN ADL5513ACPZ-R7
U55: MCP6566T-E/OT; SOT-23-5; MPN MCP6566T-E/OT
Y1: 12MHz ABM8-272-T3; Abracon_ABM8-272-T3_Crystal_SMD_3225-4Pin_3.2x2.5mm; MPN ABM8-272-T3

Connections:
1V1_ADSB: C109.1, C110.1, C111.1, U20.23 (DVDD), U20.45 (VREG_VOUT), U20.50 (DVDD)
3V0_RF_QUIET: C116.1, R86.1, R96.1, R800.1, R801.1, R840.1, R841.1, U55.5 (V+); also elsewhere on the board
3V3_ADSB: C91.1, C100.1, C101.1, C102.1, C103.1, C104.1, C105.1, C106.1, C107.1, C108.1, C113.1, R91.2, R98.2, TP20.1, U11.5 (QOD), U11.6 (VOUT), U20.1 (IOVDD), U20.10 (IOVDD), U20.22 (IOVDD), U20.33 (IOVDD), U20.42 (IOVDD), U20.43 (ADC_AVDD), U20.44 (VREG_VIN), U20.48 (USB_VDD), U20.49 (IOVDD), U21.8 (VCC); also elsewhere on the board
3V3_MAIN: U11.1 (VIN); also elsewhere on the board
ADSB_ANT: C800.1, D3.1, J7.1 (In)
ADSB_CLPF: C99.1, U54.14 (CLPF)
ADSB_CT: C90.1, U11.4 (CT)
ADSB_DET_IN: C95.1, FL2.E (OUT), R95.1
ADSB_DET_VP: C97.1, C98.1, R96.2, U54.1 (VPOS), U54.4 (VPOS)
ADSB_INHI: C95.2, U54.2 (INHI)
ADSB_INLO: C96.1, U54.3 (INLO)
ADSB_L1_BIAS: C801.1, L800.1, R800.2
ADSB_L1_IN: C800.2, U50.2 (RFIN)
ADSB_L1_OUT: C803.1, L801.2, U50.7 (RFOUT/VDD)
ADSB_L1_VD: C802.1, L801.1, R801.2
ADSB_L1_VEN: L800.2, U50.1 (VEN/VBIAS)
ADSB_L2_BIAS: C841.1, L840.1, R840.2
ADSB_L2_IN: C840.2, U52.2 (RFIN)
ADSB_L2_OUT: C843.1, L841.2, U52.7 (RFOUT/VDD)
ADSB_L2_VD: C842.1, L841.1, R841.2
ADSB_L2_VEN: L840.2, U52.1 (VEN/VBIAS)
ADSB_PULSE: R98.1, TP26.1, U20.11 (GPIO8), U55.1
ADSB_S1_IN: C803.2, FL1.B (IN)
ADSB_S1_OUT: C840.1, FL1.E (OUT)
ADSB_S2_IN: C843.2, FL2.B (IN)
ADSB_SW_EN: R90.1, U11.3 (ON); also elsewhere on the board
ADSB_TADJ: R97.1, U54.9 (TADJ)
ADSB_THR: C88.1, R86.2, R87.1, R88.2, U55.4 (-)
ADSB_THR_PWM: R88.1, U20.12 (GPIO9)
ADSB_VIDEO: R89.1, TP25.1, U54.11 (VSET), U54.12 (VOUT), U55.3 (+)
ADSB_VIDEO_ADC: R89.2, U20.38 (GPIO26/ADC0)
GND: C88.2, C90.2, C91.2, C96.2, C97.2, C98.2, C99.2, C100.2, C101.2, C102.2, C103.2, C104.2, C105.2, C106.2, C107.2, C108.2, C109.2, C110.2, C111.2, C112.2, C113.2, C114.2, C115.2, C116.2, C801.2, C802.2, C841.2, C842.2, D3.2, FL1.A (GND), FL1.C (GND), FL1.D (GND), FL1.F (GND), FL2.A (GND), FL2.C (GND), FL2.D (GND), FL2.F (GND), J7.2 (Ext), R87.2, R90.2, R95.2, R97.2, U11.2 (GND), U20.19 (TESTEN), U20.57 (GND), U21.4 (GND), U50.9 (GND), U52.9 (GND), U54.10 (COMM), U54.17 (EPAD), U55.2 (V-), Y1.2 (G), Y1.4 (G); also elsewhere on the board
QSPI_SCLK: U20.52 (QSPI_SCLK), U21.6 (CLK)
QSPI_SD0: U20.53 (QSPI_SD0), U21.5 (DI/IO_{0})
QSPI_SD1: U20.55 (QSPI_SD1), U21.2 (DO/IO_{1})
QSPI_SD2: U20.54 (QSPI_SD2), U21.3 (~WP/IO_{2})
QSPI_SD3: U20.51 (QSPI_SD3), U21.7 (~HOLD/~RESET/IO_{3})
QSPI_SS: R92.1, U20.56 (~QSPI_SS), U21.1 (~CS)
RP_RUN: C112.1, R91.1, TP22.1, U20.26 (RUN); also elsewhere on the board
RP_SWCLK: TP23.1, U20.24 (SWCLK)
RP_SWDIO: TP24.1, U20.25 (SWDIO)
RP_UART_CTS: U20.5 (GPIO3); also elsewhere on the board
RP_UART_RTS: U20.4 (GPIO2); also elsewhere on the board
RP_UART_RX: U20.2 (GPIO0); also elsewhere on the board
RP_UART_TX: U20.3 (GPIO1); also elsewhere on the board
RP_USB_DM: R99.2, TP30.1
RP_USB_DM_R: R99.1, U20.46 (USB_DM)
RP_USB_DP: R94.2, TP29.1
RP_USB_DP_R: R94.1, U20.47 (USB_DP)
RP_XIN: C114.1, U20.20 (XIN), Y1.1
RP_XOUT: R93.1, U20.21 (XOUT)
RP_XTAL_R: C115.1, R93.2, Y1.3
USB_BOOT: R92.2, TP21.1

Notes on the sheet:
09 1090 MHz chain (BLB01 x2, TA2003A x2, ADL5513, MCP6566) and RP2040 capture
Chain per docs/ADSB_VALIDATION.md. BLB01 bias per BeRex rev 6.6 evaluation BOM (C1 100pF in, C2 12pF out, R1 6.8k/C3 12pF/L1 27nH Ven, R2 0R/C4 100pF/L2 82nH Vd).
ADL5513 measurement mode (VSET=VOUT), 52.3R input termination, 47nF coupling. TADJ resistor and CLPF (1 nF basic value is too slow for 0.5 us pulses) are TBD/bench items.
MCP6566T-E/OT base pin map, 2.2k pull-up to the RP2040 bank. A2: threshold = filtered RP2040 PWM (R88/C88/R87) with ADSB_VIDEO also sampled on ADC0 (R89); fixed-divider top R86 stays DNP (OWN-09 target still open).
RP2040 per DIG-01 (Raspberry Pi minimal design): 12 MHz ABM8-272-T3 + 1k XOUT, 15pF loads; QSPI_SS 1k to USB_BOOT pad; RUN 10k/100nF + TCA9535 P14. Domain 3V3_ADSB switched (P13). A2: USB D+/D- on test pads through 27R so BOOTSEL (TP21) is usable.
UART0: GPIO0 TX -> RP_UART_RX, GPIO1 RX <- RP_UART_TX, GPIO2 CTS <- RP_UART_RTS, GPIO3 RTS -> RP_UART_CTS (one-shot pin choice). Back-power of ESP32-driven lines into an OFF RP2040 is an open SYS-02 item.
